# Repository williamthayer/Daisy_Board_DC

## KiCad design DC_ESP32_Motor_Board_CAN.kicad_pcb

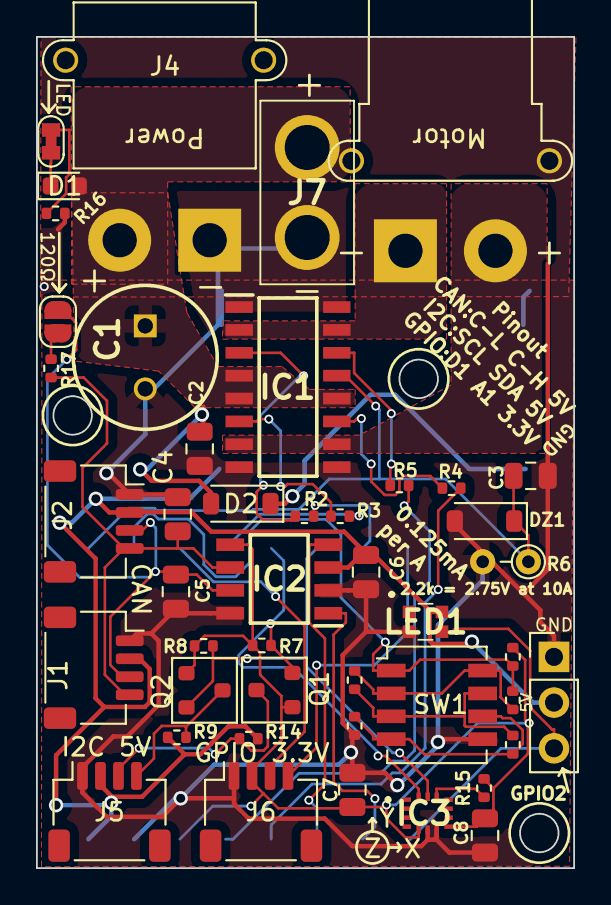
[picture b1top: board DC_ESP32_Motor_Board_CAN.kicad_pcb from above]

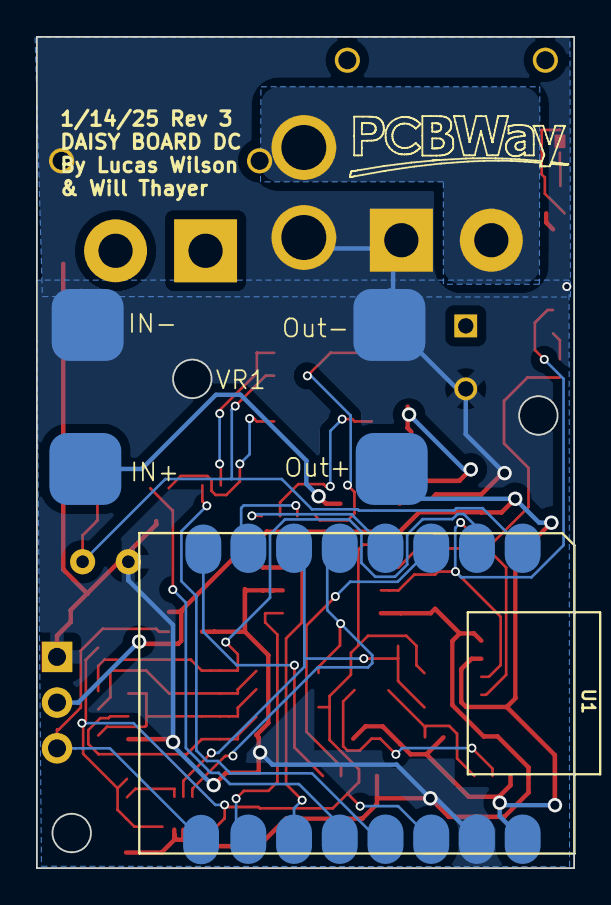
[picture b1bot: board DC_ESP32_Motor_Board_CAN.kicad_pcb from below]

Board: 2 copper layers, 29.8 x 46.2 mm, 47 parts (2 on the bottom side), 35 nets.

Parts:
C1: EEU-FK1E271; CAPPRD350W65D800H1300
C2, C6, C7, C8: 100nF; C_0805_2012Metric
C3: 10nF; C_0805_2012Metric
C4, C5: 30pF; C_0805_2012Metric
D1: KT-0603R; LED_0603_1608Metric
D2: SS34; D_SOD-123
DZ1: MM1Z3V3; D_SOD-123
IC1: VNH7100BASTR; SOIC127P600X175-16N
IC2: TJA1050T_CM; SOIC127P600X175-8N
IC3: LSM6DS3TR-C; LSM6DS3USTR
J1, J2, J5, J6: SM04B-SRSS-TB; JST_SH_SM04B-SRSS-TB_1x04-1MP_P1.00mm_Horizontal
J3: XT30PB; xt30_90_Female
J4: XT30PB; Xt30 Horizontal
J7: XT30PB
J8: Conn_01x03_Pin; PinHeader_1x03_P2.54mm_Vertical
JP1: SolderJumper_2_Open; SolderJumper-2_P1.3mm_Open_RoundedPad1.0x1.5mm
JP2: SolderJumper_2_Open; Jumper Connected 2 Pin Small
LED1: WS2812C-2020; WS2812C2020
Q1, Q2: BSS138; SOT-23
R1: 22k; R_0402_1005Metric
R2, R3, R4, R5: 1.1k; R_0402_1005Metric
R6: Rsense; R_Axial_DIN0204_L3.6mm_D1.6mm_P2.54mm_Vertical
R7, R8, R9, R10, R13, R14, R15: 10k; R_0402_1005Metric
R11: 4.7k; R_0402_1005Metric
R12: 2.2k; R_0402_1005Metric
R16: 1.5k; R_0402_1005Metric
R17: 120; R_0402_1005Metric
SW1: DSHP04TJGER; SW_DIP_SPSTx04_Slide_Copal_CHS-04A_W5.08mm_P1.27mm_JPin
U1: MOUDLE-SEEEDUINO-XIAO-ESP32C3; ESP32-C3 16 Pin Super Mini
VR1: EY9 reg board

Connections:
+3.3V: C7.1, C8.1, IC2.5 (VREF), IC3.5 (VDDIO), IC3.8 (VDD), J6.2, Q1.1 (G), Q2.1 (G), R7.2, R8.2, R13.1, R15.2, U1.14 (3.3V)
+5V: C6.1, IC2.3 (VCC), J1.2, J2.2, J5.2, J8.2, LED1.4 (VDD), R9.2, R14.2, U1.16 (5V), VR1.2 (Out+)
+24V: C1.1 (+), C2.1, D1.2 (A), D2.2 (A), IC1.4 (VCC_1), IC1.5 (VCC_2), IC1.12 (VCC_3), J4.2, J7.2
/OUTA: IC1.2 (OUTA_1), IC1.15 (OUTA_2), J3.1
/OUTB: IC1.7 (OUTB_1), IC1.10 (OUTB_2), J3.2
/SCL5: J5.4, Q2.3 (D), R9.1
/SDA5: J5.3, Q1.3 (D), R14.1
CANH: C5.1, IC2.7 (CANH), J1.3, J2.3, JP1.2 (B)
CANL: C4.2, IC2.6 (CANL), J1.4, J2.4, R17.1
CANRX: IC2.4 (RXD), U1.11 (PA6_A10_D10_MOSI)
CANTX: IC2.1 (TXD), U1.10 (PA5_A9_D9_MISO)
DipV: R1.2, R13.2, SW1.1, U1.2 (PA4_A1_D1)
GND: C1.2 (-), C2.2, C3.2, C4.1, C5.2, C6.2, C7.2, C8.2, DZ1.2 (A), IC1.1 (GNDA_1), IC1.8 (GNDB_1), IC1.9 (GNDB_2), IC1.16 (GNDA_2), IC2.2 (GND), IC2.8 (S), IC3.6 (GND_1), IC3.7 (GND_2), J1.1, J2.1, J4.1, J5.1, J6.1, J7.1, J8.1, LED1.2 (GND), R6.2, R12.1, R16.1, SW1.5, U1.15 (GND), VR1.1 (Out-), VR1.4 (In-)
GPIO_1: J6.4, U1.8 (PB09_A7_D7_RX)
GPIO_2: J8.3, LED1.3 (DI), U1.9 (PA7_A8_D8_SCK)
GPIO_A: J6.3, U1.3 (PA10_A2_D2)
INA: R2.1, U1.7 (PB08_A6_D6_TX)
INB: R3.1, U1.4 (PA11_A3_D3)
unnamed: D1.1 (K), JP2.2 (B)
unnamed: D2.1 (K), VR1.3 (In+)
unnamed: IC1.3 (INA), R2.2
unnamed: IC1.6 (INB), R3.2
unnamed: IC1.11 (PWM), R4.1
unnamed: IC1.14 (SEL0), R5.1
unnamed: IC3.12 (CS), R15.1
unnamed: JP1.1 (A), R17.2
unnamed: JP2.1 (A), R16.2
unnamed: R1.1, R10.2, SW1.2, SW1.8
unnamed: R10.1, R11.2, SW1.3, SW1.7
unnamed: R11.1, R12.2, SW1.4, SW1.6
PWM: R4.2, U1.12 (PA6_A11_D11)
RSENSE: C3.1, DZ1.1 (K), IC1.13 (CS), R6.1, U1.1 (PA02_A0_D0)
SCL: IC3.13 (SCL), Q2.2 (S), R8.1, U1.6 (PA9_A5_D5_SCL)
SDA: IC3.14 (SDA), Q1.2 (S), R7.1, U1.5 (PA8_A4_D4_SDA)
SEL: R5.2, U1.13 (PA6_A12_D12)

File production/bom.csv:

Designator,Footprint,Quantity,Value,LCSC Part #
"C2, C6, C7, C8",0805,4,100nF,
C3,0805,1,10nF,
"C4, C5",0805,2,30pF,
D1,0603,1,KT-0603R,
D2,D_SOD-123,1,SS34,
DZ1,D_SOD-123,1,MM1Z3V3,
IC1,SOIC127P600X175-16N,1,VNH7100BASTR,
IC2,SOIC127P600X175-8N,1,TJA1050T_CM,
IC3,LSM6DS3USTR,1,LSM6DS3TR-C,
"J1, J2, J5, J6",JST_SH_SM04B-SRSS-TB_1x04-1MP_P1.00mm_Horizontal,4,SM04B-SRSS-TB,
"Q1, Q2",SOT-23,2,BSS138,
R1,0402,1,22k,
"R10, R13, R14, R15, R7, R8, R9",0402,7,10k,
R11,0402,1,4.7k,
R12,0402,1,2.2k,
R16,0402,1,1.5k,
R17,0402,1,120,
"R2, R3, R4, R5",0402,4,1.1k,
SW1,SW_DIP_SPSTx04_Slide_Copal_CHS-04A_W5.08mm_P1.27mm_JPin,1,DSHP04TJGER,

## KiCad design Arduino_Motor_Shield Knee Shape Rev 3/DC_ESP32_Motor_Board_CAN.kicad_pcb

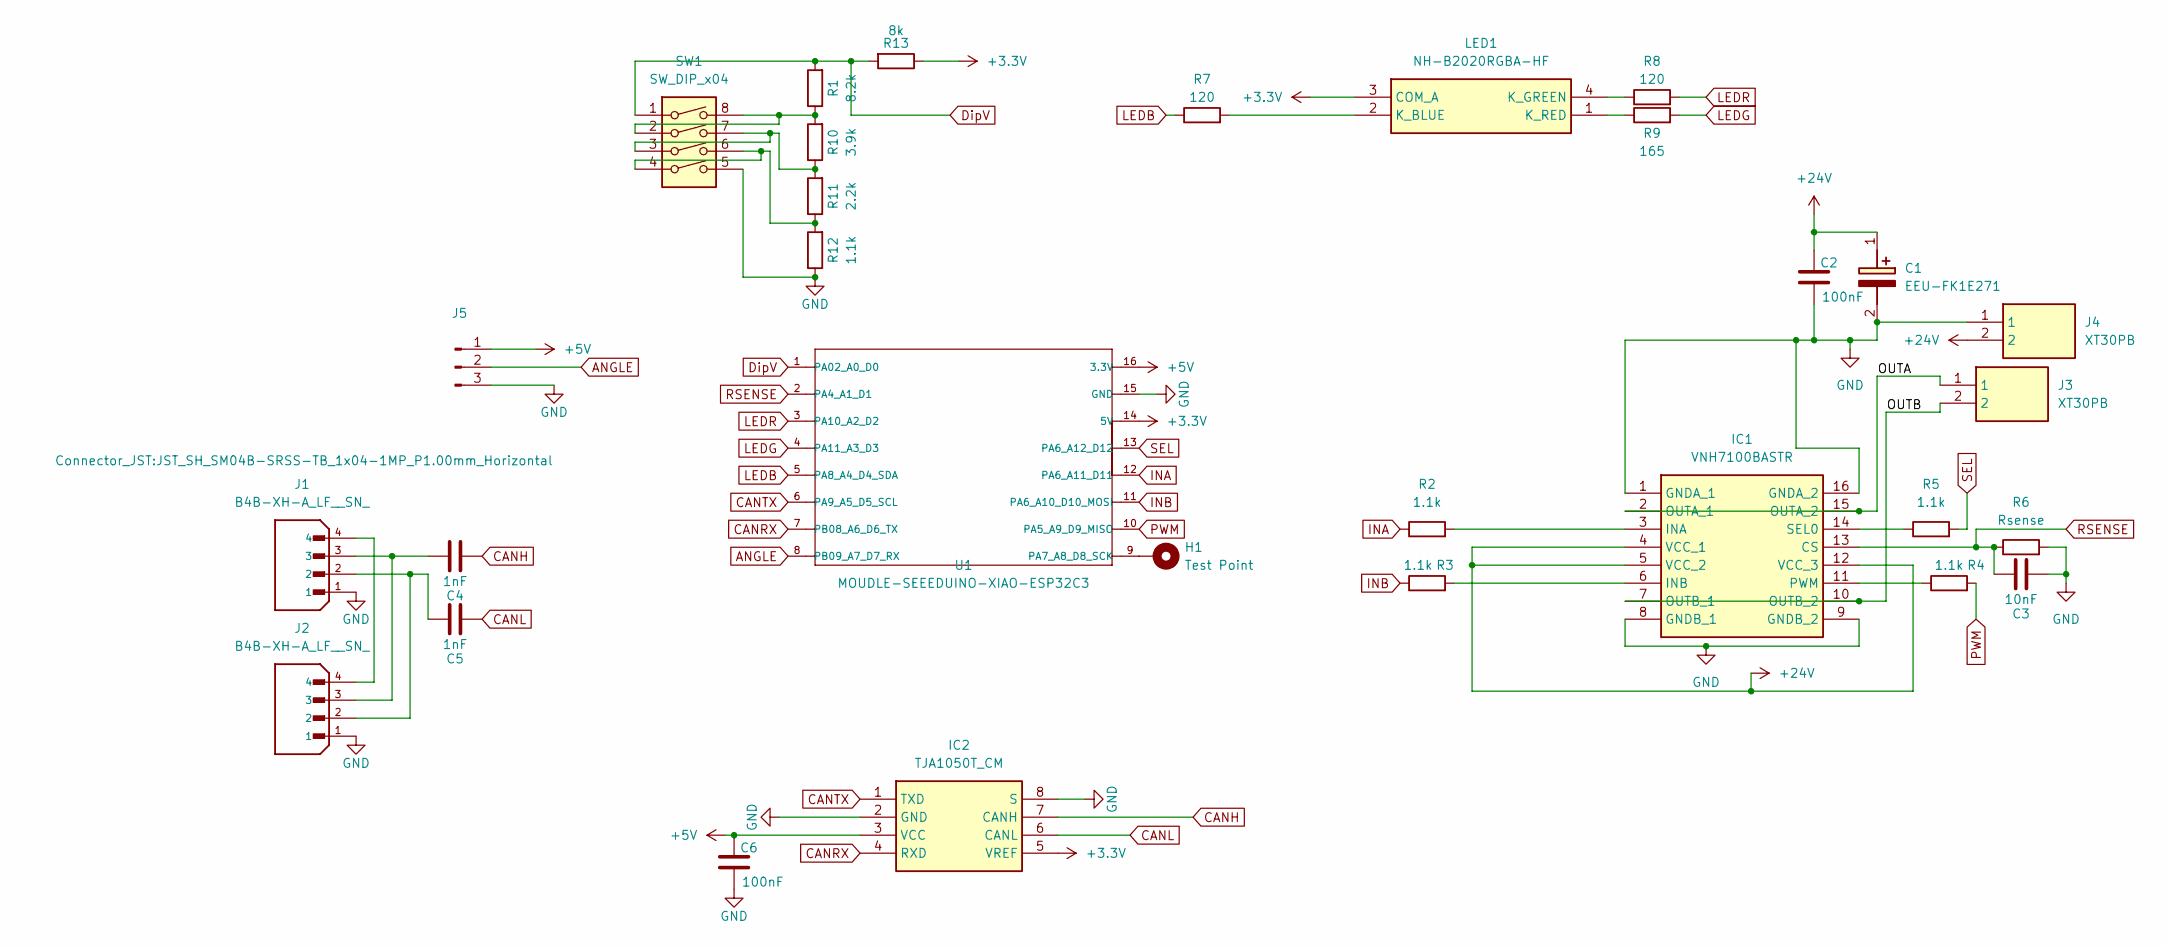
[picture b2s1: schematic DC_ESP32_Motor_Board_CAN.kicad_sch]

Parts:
C1: EEU-FK1E271; CAPPRD350W65D800H1300; Manufacturer_Part_Number EEU-FK1E271; Mouser Part Number 667-EEU-FK1E271
C2, C6: 100nF; C_0805_2012Metric
C3: 10nF; C_0805_2012Metric
C4, C5: 1nF; C_0805_2012Metric
H1: Test Point; TestPoint_Keystone_5015_Micro-Minature
IC1: VNH7100BASTR; SOIC127P600X175-16N; Manufacturer_Part_Number VNH7100BASTR; Mouser Part Number 511-VNH7100BASTR
IC2: TJA1050T_CM; SOIC127P600X175-8N; Manufacturer_Part_Number TJA1050T/CM; Mouser Part Number N/A
J1, J2: B4B-XH-A_LF__SN_; JST_SH_SM04B-SRSS-TB_1x04-1MP_P1.00mm_Horizontal
J3, J4: XT30PB; AMASS_XT30PW-M_1x02_P2.50mm_Horizontal; Manufacturer_Part_Number XT30PB
J5: Conn_01x03_Pin; JST_SH_SM03B-SRSS-TB_1x03-1MP_P1.00mm_Horizontal
LED1: NH-B2020RGBA-HF; Manufacturer_Part_Number NH-B2020RGBA-HF
R1: 8.2k; R_0402_1005Metric
R2, R3, R4, R5, R12: 1.1k; R_0402_1005Metric
R6: Rsense; R_Axial_DIN0204_L3.6mm_D1.6mm_P5.08mm_Horizontal
R7, R8: 120; R_0402_1005Metric
R9: 165; R_0402_1005Metric
R10: 3.9k; R_0402_1005Metric
R11: 2.2k; R_0402_1005Metric
R13: 8k; R_0402_1005Metric
SW1: SW_DIP_x04; SW_DIP_SPSTx04_Slide_KingTek_DSHP04TJ_W5.25mm_P1.27mm_JPin
U1: MOUDLE-SEEEDUINO-XIAO-ESP32C3; MOUDLE14P-SMD-2.54-21X17.8MM

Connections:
+24V: C1.1 (+), C2.1, IC1.4 (VCC_1), IC1.5 (VCC_2), IC1.12 (VCC_3), J4.2
/OUTA: IC1.2 (OUTA_1), IC1.15 (OUTA_2), J3.1
/OUTB: IC1.7 (OUTB_1), IC1.10 (OUTB_2), J3.2
ANGLE: J5.2, U1.8 (PB09_A7_D7_RX)
CANH: C4.2, IC2.7 (CANH)
CANL: C5.2, IC2.6 (CANL)
CANRX: IC2.4 (RXD), U1.7 (PB08_A6_D6_TX)
CANTX: IC2.1 (TXD), U1.6 (PA9_A5_D5_SCL)
DipV: R1.2, R13.2, SW1.1, U1.1 (PA02_A0_D0)
GND: C1.2 (-), C2.2, C3.2, C6.2, IC1.1 (GNDA_1), IC1.8 (GNDB_1), IC1.9 (GNDB_2), IC1.16 (GNDA_2), IC2.2 (GND), IC2.8 (S), J1.1, J2.1, J4.1, J5.3, R6.2, R12.1, SW1.5, U1.15 (GND)
INA: R2.1, U1.12 (PA6_A11_D11)
INB: R3.1, U1.11 (PA6_A10_D10_MOSI)
LEDB: R7.1, U1.5 (PA8_A4_D4_SDA)
LEDG: R9.2, U1.4 (PA11_A3_D3)
LEDR: R8.2, U1.3 (PA10_A2_D2)
unnamed: C4.1, J1.3, J2.3
unnamed: C5.1, J1.2, J2.2
unnamed: IC1.3 (INA), R2.2
unnamed: IC1.6 (INB), R3.2
unnamed: IC1.11 (PWM), R4.1
unnamed: IC1.14 (SEL0), R5.1
unnamed: J1.4, J2.4
unnamed: LED1.2 (K_BLUE), R7.2
unnamed: LED1.4 (K_GREEN), R8.1
unnamed: LED1.1 (K_RED), R9.1
unnamed: R1.1, R10.2, SW1.2, SW1.8
unnamed: R10.1, R11.2, SW1.3, SW1.7
unnamed: R11.1, R12.2, SW1.4, SW1.6
unnamed: H1.1, U1.9 (PA7_A8_D8_SCK)
PWM: R4.2, U1.10 (PA5_A9_D9_MISO)
RSENSE: C3.1, IC1.13 (CS), R6.1, U1.2 (PA4_A1_D1)
SEL: R5.2, U1.13 (PA6_A12_D12)

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
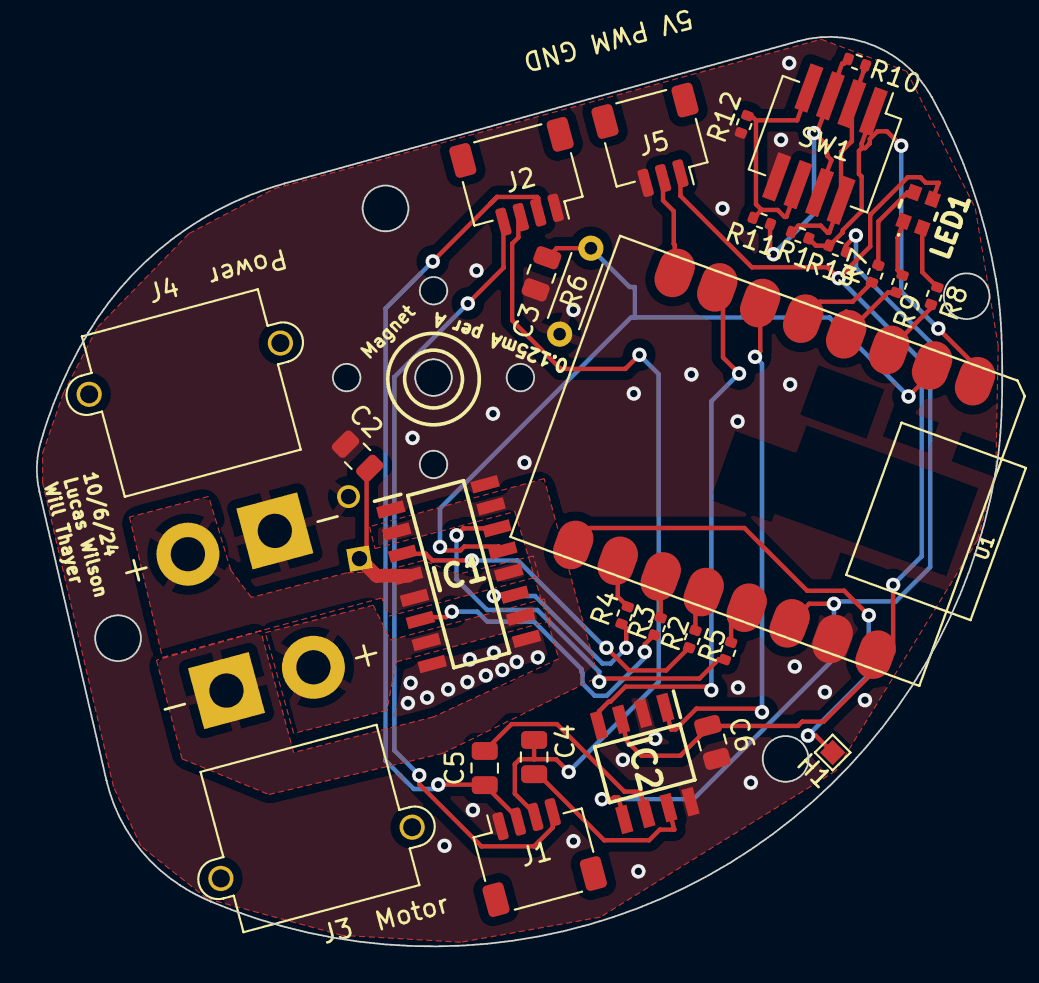
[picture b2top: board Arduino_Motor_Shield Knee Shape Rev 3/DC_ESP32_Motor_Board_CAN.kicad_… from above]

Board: 2 copper layers, 53.6 x 50.5 mm, 30 parts (1 on the bottom side), 34 nets.

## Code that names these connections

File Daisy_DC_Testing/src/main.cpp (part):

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#define freqAngle 10      // PID timer interup frequency (Hz)
#define freqCurrent 100   // current timer interup frequency (Hz)
#define currentAVGSize 10 // How many samples to use in the current rolling average filter
#define angleAVGSize 10   // How many samples to use in the angle rolling average filter
#define rSize 2200        // Size of resistor used for current feedback in ohms
#define CANRXID 100       // ID for CAN receiving
#define CANTXID 101       // ID for CAN sending
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#define PIN_CAN_TX 1
#define PIN_CAN_RX 2
#define PIN_PWM 3
#define PIN_SEL 4
#define PIN_RSENSE 5
#define PIN_DIP_V 6
#define PIN_GPIO_A 7
#define PIN_INB 8
#define PIN_SDA 9
#define PIN_SCL 10
#define PIN_INA 20
#define PIN_GPIO1 21

// Modes:
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
// PID variables
double targetAngle = 180.0; // Desired target angle (0-360 degrees)
double pidInputAngle = 0;   // Current angle (feedback)
double pidOutputAngle = 0;  // PID output (motor control signal)
// PID variables
double targetCurrent = 500;  // Desired target current (mA)
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}
void driveMotor(bool INA, bool INB, int PWM) // control H-Bridge motor driver
{
  digitalWrite(PIN_INA, INA);
  digitalWrite(PIN_INB, INB);
  analogWrite(PIN_PWM, PWM);
}
int getAngle(bool avg = false)
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int getCurrent(bool avg = false) // Return the current in mA with or without a 8 sample avg
{
  int adjustment = rSize * 100 / 293;
  long currentMa = analogRead(PIN_RSENSE) * rSize / adjustment;

  static long sum;
  static int currentIndex = 0;
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void IRAM_ATTR angleMicroISR()//Triggered interrupt form angle signal
{
  static uint32_t riseTime;
  if (digitalRead(PIN_GPIO_A) == HIGH)
    riseTime = micros();
  else
  {
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}
void setupPins()
{
  pinMode(PIN_INA, OUTPUT);
  pinMode(PIN_INB, OUTPUT);
  pinMode(PIN_PWM, OUTPUT);
  attachInterrupt(PIN_GPIO_A, angleMicroISR, CHANGE);

  // Timer for Angle PID
  timerAngle = timerBegin(0, 80, true); // Timer 0, prescaler 80 (1 µs tick)
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
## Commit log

2024-10-24 Rev A
2024-10-29 Update with mounting holes
2024-11-21 Last Update to PCBWAY
2024-11-21 Added DataSheet
2024-12-20 Code Added
    Code added to repo
2025-01-02 Code Updates
2025-01-07 Code updates
    Code for Lucus
2025-01-07 Updates for PCB
    Bigger GPIO2
    Added RGB LED
    Updated xt30s
    Updated xt30 size to fit inline connectors on PCB
    Fixed jst sh connections
2025-01-08 Minor Trace Updates
2025-01-15 Newest Update for Review
    Updated do not place parts, and fixed last last few traces. Should be good for ordering
